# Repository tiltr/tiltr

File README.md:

# wheely_good_robot
Repo for the ROS components of the bigger balance bot (and dockerfiles for the dev environment)

## How to build

```bash
docker build . -t tiltr/base-dev:latest
docker build - < Dockerfile_add_cartographer -t tiltr/cartographer-dev:latest
./nvidialise2.sh tiltr/cartographer-dev:latest
docker create --privileged --net=host -it --gpus all -v /tmp/.X11-unix:/tmp/.X11-unix -e DISPLAY -e QT_X11_NO_MITSHM=1 -e XDG_RUNTIME_DIR=/run/user/1000 -e LOCAL_USER_ID=$(id -u) --name tilter_cartographer tiltr/cartographer-dev:latest-nvidia2
docker start tilter_cartographer
```

or

```bash
./build_all.sh
docker start tilter_cartographer
```

## Build environment

Arduino works, but currently trialing cubemx/truestudio for cmsis HAL 

https://www.st.com/content/st_com/en/products/development-tools/software-development-tools/stm32-software-development-tools/stm32-ides/truestudio.html?dl=qX3dxD%2FV1ClpPeuPcbo%2B4A%3D%3D%2C%2FAqFiBs1j2XeHmjlAo2c5Q4gXjxwqLaEqWSJTHkfdtBOFQaaKZwvb7V4Wqy03aTzzwJGmsU46NqtHsX%2FygKpD15DJcwN%2FTnM48NXqntLk%2FgAtCWlzJEDYmUuYtbE3Gomv9r56FefeYTppl4HVKNh8%2F8yPZmZ6AAH5iyDjEHXRHppx8rQ%2BEIj3pNXepH6F79qX%2BdHf30Du4PAkvLM1Ra26eqRB2xN1BFKctqo8v%2B049yN65LwYpnL%2FGwowx4BAYooDVxzW6QiAo9rJNUCt6VtOpKM4tG9zI9%2BM3ZqphD9Owb1LR9PSaxss3x5Um1D7uAmmwnaUiRj2M8FcE61PY1Ah0AUO3T24WniPfP80%2F8JDmA%3D&uid=8cLceiBTYxUTRYysFZmtS71WMKIsWRCC

https://www.st.com/en/development-tools/stm32cubemx.html#get-software

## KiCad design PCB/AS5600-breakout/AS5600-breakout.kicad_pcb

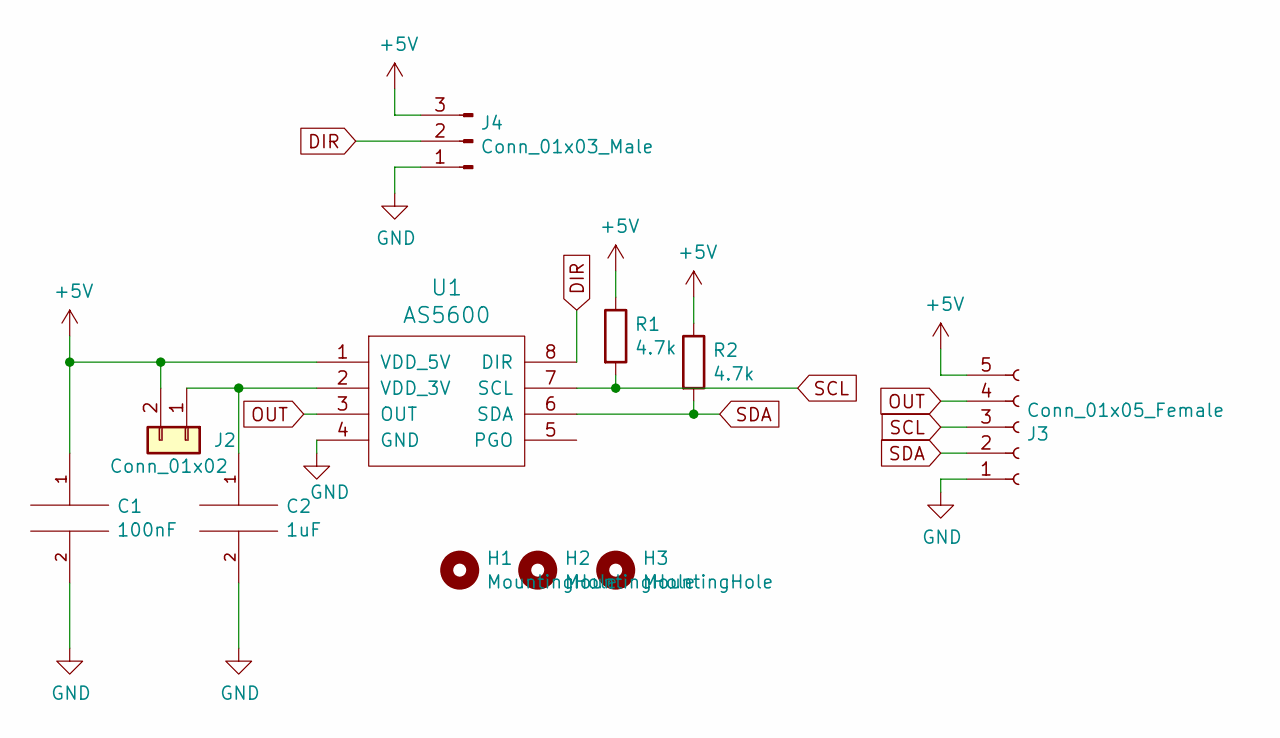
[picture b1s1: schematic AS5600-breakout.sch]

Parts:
C1: 100nF; C_Disc_D4.7mm_W2.5mm_P5.00mm
C2: 1uF; CP_Radial_D5.0mm_P2.00mm
H1, H2, H3: MountingHole; MountingHole_2.2mm_M2_small
J2: Conn_01x02; PinHeader_1x02_P2.54mm_Vertical
J3: Conn_01x05_Female; Molex_KK-254_AE-6410-05A_1x05_P2.54mm_Vertical
J4: Conn_01x03_Male; SOIC127_solder_switch
R1, R2: 4.7k; R_Axial_DIN0207_L6.3mm_D2.5mm_P7.62mm_Horizontal
U1: AS5600; SOIC127P600X175-8N

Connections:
+5V: C1.1, J2.2, J3.5, J4.3, R1.1, R2.1, U1.1 (VDD_5V)
DIR: J4.2, U1.8 (DIR)
GND: C1.2, C2.2, J3.1, J4.1, U1.4 (GND)
unnamed: C2.1, J2.1, U1.2 (VDD_3V)
OUT: J3.4, U1.3 (OUT)
SCL: J3.3, R1.2, U1.7 (SCL)
SDA: J3.2, R2.2, U1.6 (SDA)

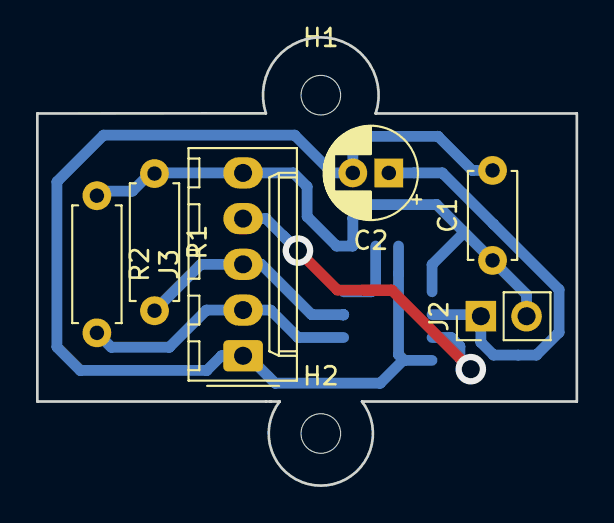
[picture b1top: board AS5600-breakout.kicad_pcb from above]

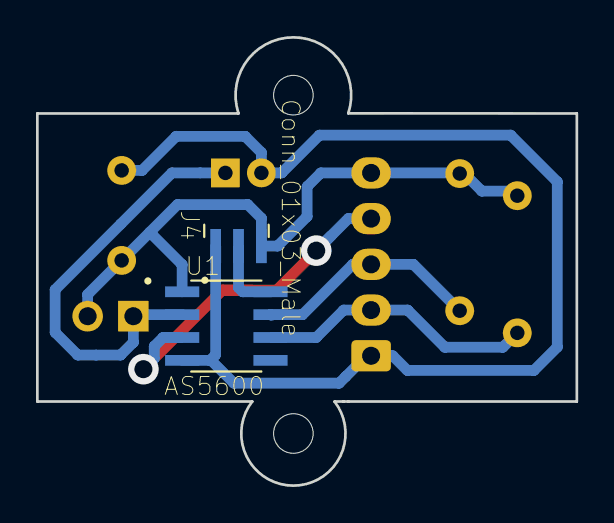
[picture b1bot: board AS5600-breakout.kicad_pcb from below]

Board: 2 copper layers, 30.0 x 24.9 mm, 10 parts (2 on the bottom side), 7 nets.

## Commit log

2019-05-23 initial commit, Dockerfile with tom_setup & cartographer installation
2019-05-23 added download sh for test bag
2019-05-23 runs now
2019-05-23 v1 building
2019-05-23 added nvidialise script (host) and run demo script (container)
2019-05-23 tidying
2019-05-23 added rplidar driver
2019-05-24 forked so I can have custom launch files
2019-05-24 not sure
2019-05-25 added user to dialout
2019-05-29 adding arduino (teensy) sketch with imu publisher. Still needs covariences
2019-05-29 added stls for motormount-dowel, shaftcoupler-dowel and motormount
2019-06-05 adding initial PCB file (with sensoe schematic & footprint), as well as Sam/Elliots CAD and the start of the frame
2019-06-05 initial PCB for encoder
2019-06-18 first pcb has been cut for encoders, looks good!
2019-07-28 working AS5600 sketch
2019-07-28 big update, commit more often!
2019-08-10 working bipropellent api control from arduino
2019-08-10 start of PID
2019-08-11 updated dockerfile
2019-08-11 updating to add stm to arduino cores
2019-08-27 Update Dockerfile
2020-02-16 added/fixed Dockerfile_no_cartographer
2020-02-16 smol bugfix
2020-02-17 Split dockerfile, now base image (Dockerfile) that builds for all but cartographer, and then 'Dockerfile_add_cartographer' calls the base and builds on it
2020-02-17 now 'Dockerfile'
2020-02-17 failed attempt to build with mbed/arduino on platformio
2020-02-17 added second Dockerfile 'add_cartographer', designed to inherit from main tiltr/base-dev Dockerfile
2020-02-17 unify layers, untested but tiny change (last commit was tested & works)
2021-03-21 add links
2022-09-30 fix first gpg key
2022-09-30 fix for 2022
2022-09-30 tested 2022, works
